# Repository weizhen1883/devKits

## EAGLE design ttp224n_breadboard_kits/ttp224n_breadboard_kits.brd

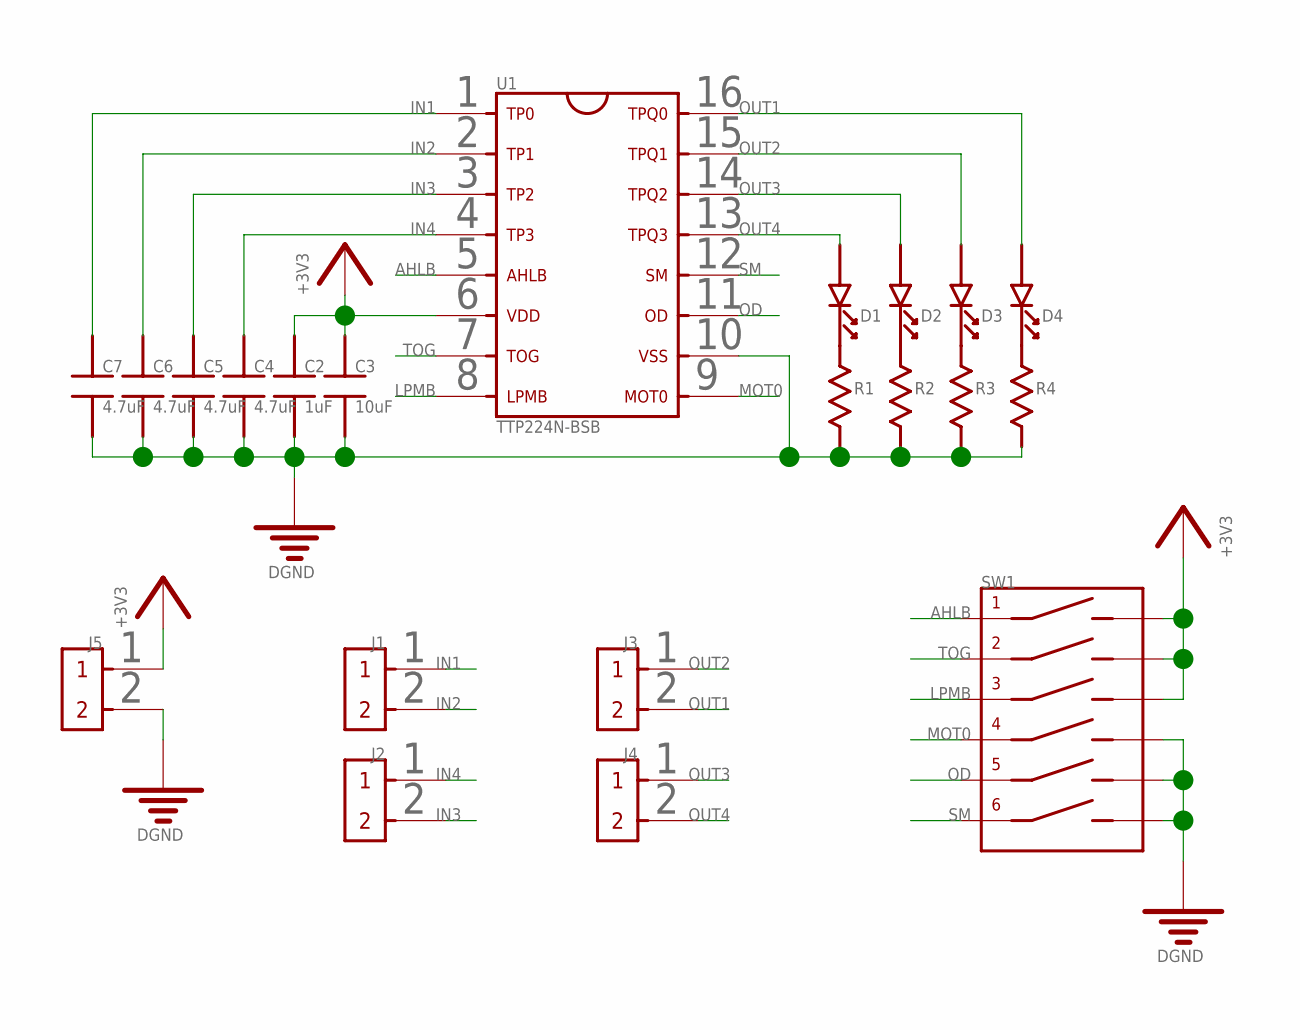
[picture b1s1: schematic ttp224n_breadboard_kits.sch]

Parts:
C2: 1uF; 0805
C3: 10uF; 0805
C4, C5, C6, C7: 4.7uF; 0805
D1, D2, D3, D4: LED-0805; 0805DIODE
J1, J2, J3, J4, J5: 2PIN_HEADER_PITCH2.54MM_TH
R1, R2, R3, R4: RESISTOR_0805; 0805
SW1: DIP_SWITCH_6PIN-219-6MST; DIP_SW_219-6MST
U1: TTP224N-BSB; SSOP-16

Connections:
+3V3: C2.1, C3.1, J5.1, SW1.2 (1.1), SW1.4 (2.1), SW1.6 (3.1), U1.6
AHLB: SW1.1 (1.0), U1.5
DGND: C2.2, C3.2, C4.2, C5.2, C6.2, C7.2, J5.2, R1.2, R2.2, R3.2, R4.2, SW1.8 (4.1), SW1.10 (5.1), SW1.12 (6.1), U1.10
IN1: C7.1, J1.1, U1.1
IN2: C6.1, J1.2, U1.2
IN3: C5.1, J2.2, U1.3
IN4: C4.1, J2.1, U1.4
LPMB: SW1.5 (3.0), U1.8
MOT0: SW1.7 (4.0), U1.9
unnamed: D1.1 (K), R1.1
unnamed: D2.1 (K), R2.1
unnamed: D3.1 (K), R3.1
unnamed: D4.1 (K), R4.1
OD: SW1.9 (5.0), U1.11
OUT1: D4.2 (A), J3.2, U1.16
OUT2: D3.2 (A), J3.1, U1.15
OUT3: D2.2 (A), J4.1, U1.14
OUT4: D1.2 (A), J4.2, U1.13
SM: SW1.11 (6.0), U1.12
TOG: SW1.3 (2.0), U1.7

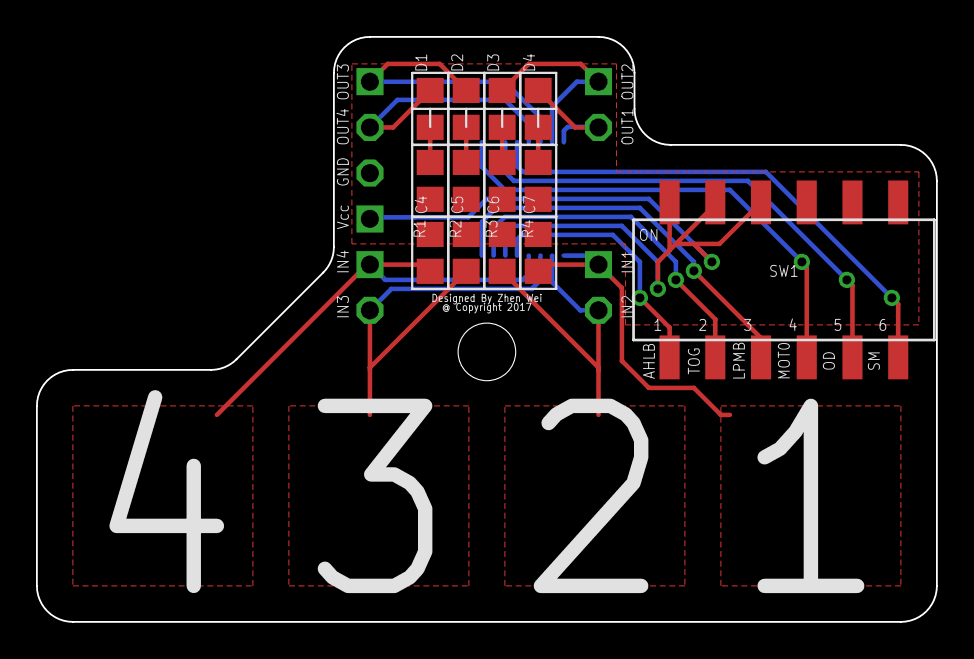
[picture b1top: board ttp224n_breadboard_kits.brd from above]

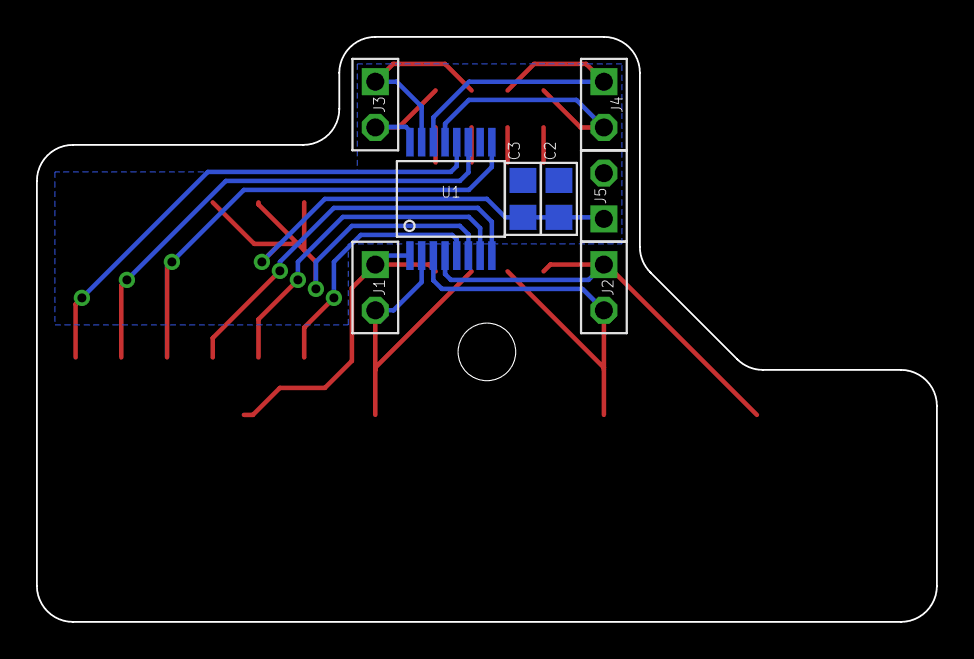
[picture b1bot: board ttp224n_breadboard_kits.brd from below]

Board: 2 copper layers, 50.0 x 32.5 mm, 21 parts (8 on the bottom side), 20 nets.

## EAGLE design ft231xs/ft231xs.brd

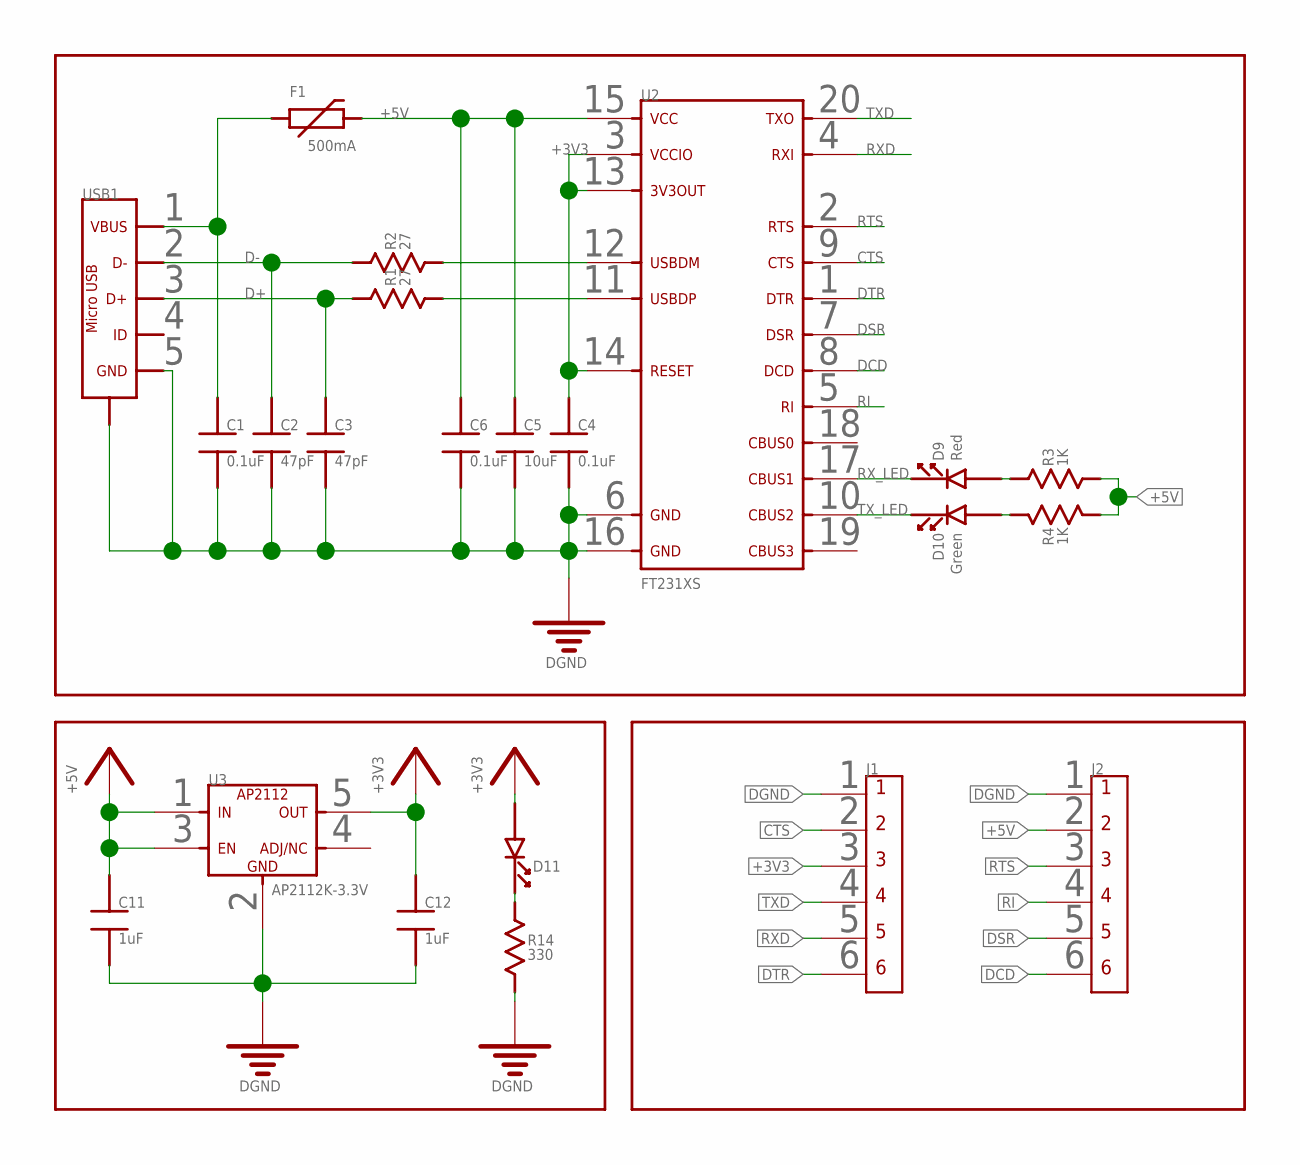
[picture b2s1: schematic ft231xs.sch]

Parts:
C1, C4, C6: 0.1uF; 0805
C2, C3: 47pF; 0805
C5: 10uF; 0805
C11, C12: 1uF; 0805
D9: Red; 0805DIODE
D10: Green; 0805DIODE
D11: LED-0805; 0805DIODE
F1: 500mA; 0805
J1, J2: 6PIN_HEADER_PITCH2.54MM_TH
R1, R2: 27; 0805
R3, R4: 1K; 0805
R14: 330; 0805
U2: FT231XS_SSOP20; SSOP-20
U3: AP2112K-3.3V; SOT-23-5
USB1: USB-2.0-MICRO_SMD_SMD; MICRO-USB-B-SMD-SMD

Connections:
+3V3: C4.1, C12.1, D11.2 (A), J1.3, U2.3, U2.13, U2.14, U3.5
+5V: C5.1, C6.1, C11.1, F1.2, J2.2, R3.2, R4.2, U2.15, U3.1, U3.3
CTS: J1.2, U2.9
D+: C3.1, R1.1, USB1.3 (D+)
D-: C2.1, R2.1, USB1.2 (D-)
DCD: J2.6, U2.8
DGND: C1.2, C2.2, C3.2, C4.2, C5.2, C6.2, C11.2, C12.2, J1.1, J2.1, R14.2, U2.6, U2.16, U3.2, USB1.5 (GND), USB1.M1 (SHIELD), USB1.M2 (SHIELD), USB1.M3 (SHIELD), USB1.M4 (SHIELD), USB1.S1 (SHIELD), USB1.S2 (SHIELD)
DSR: J2.5, U2.7
DTR: J1.6, U2.1
unnamed: R2.2, U2.12
unnamed: R1.2, U2.11
unnamed: D9.2 (A), R3.1
unnamed: D10.2 (A), R4.1
unnamed: D11.1 (K), R14.1
RI: J2.4, U2.5
RTS: J2.3, U2.2
RXD: J1.5, U2.4
RX_LED: D9.1 (K), U2.17
TXD: J1.4, U2.20
TX_LED: D10.1 (K), U2.10
VBUS: C1.1, F1.1, USB1.1 (VBUS)

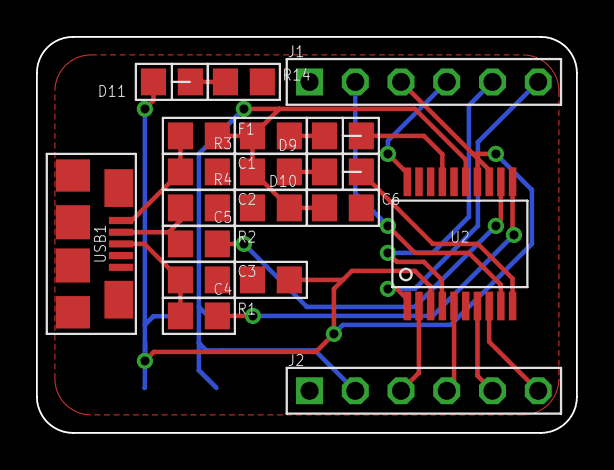
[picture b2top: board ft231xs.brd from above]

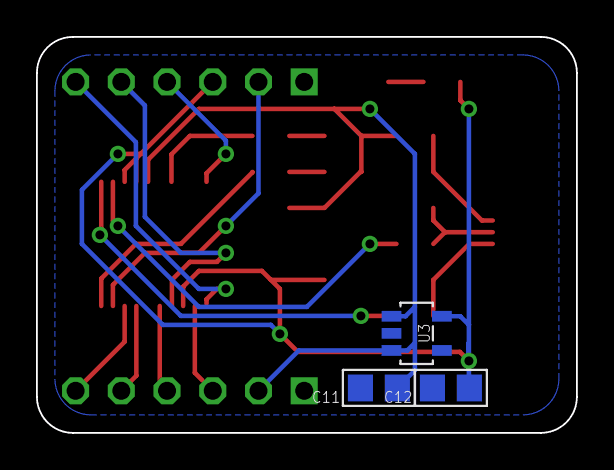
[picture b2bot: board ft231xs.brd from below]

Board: 2 copper layers, 30.0 x 22.0 mm, 22 parts (3 on the bottom side), 21 nets.

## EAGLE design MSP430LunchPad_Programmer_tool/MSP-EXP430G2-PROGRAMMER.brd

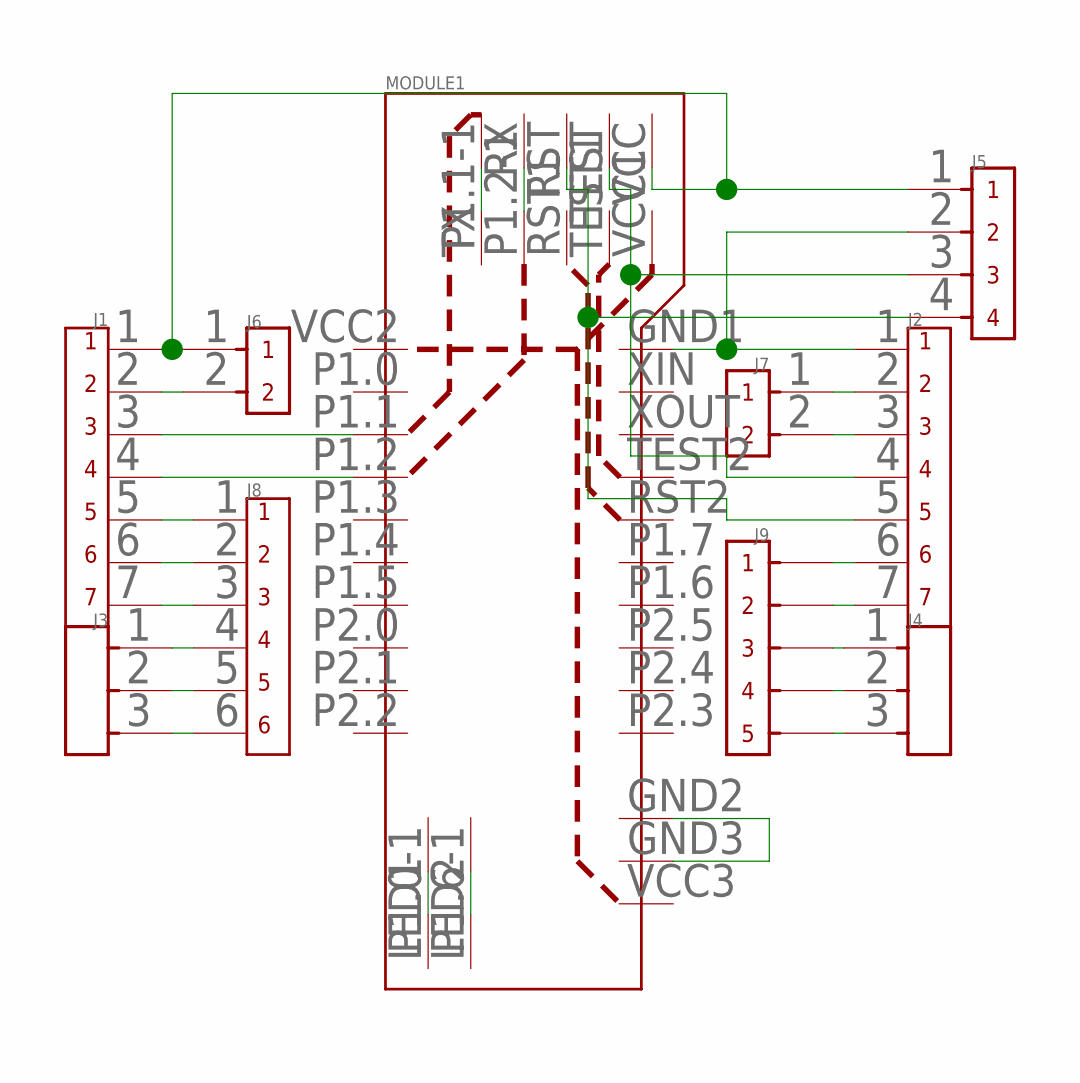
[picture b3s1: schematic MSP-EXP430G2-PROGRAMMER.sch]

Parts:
J1, J2: 7PIN_HEADER_PITCH2.54MM_TH
J3, J4: 3PIN_HEADER_PITCH2.54MM_TH
J5: 4PIN_HEADER_PITCH2.54MM_TH
J6, J7: 2PIN_HEADER_PITCH2.54MM_TH
J8: 6PIN_HEADER_PITCH2.54MM_TH
J9: 5PIN_HEADER_PITCH2.54MM_TH
MODULE1: MSP-EXP430G2-SHELL

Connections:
DGND: J2.1, J5.2, MODULE1.GND1, MODULE1.GND2, MODULE1.GND3
unnamed: J1.3, MODULE1.P1.1
unnamed: J1.4, MODULE1.P1.2
unnamed: MODULE1.P1.1-1, MODULE1.TX
unnamed: MODULE1.P1.2-1, MODULE1.RX
unnamed: J1.2, J6.2
unnamed: J1.5, J8.1
unnamed: J1.6, J8.2
unnamed: J1.7, J8.3
unnamed: J3.1, J8.4
unnamed: J3.2, J8.5
unnamed: J3.3, J8.6
unnamed: J2.2, J7.1
unnamed: J2.3, J7.2
unnamed: J2.6, J9.1
unnamed: J2.7, J9.2
unnamed: J4.1, J9.3
unnamed: J4.2, J9.4
unnamed: J4.3, J9.5
unnamed: MODULE1.LED1 (LED0), MODULE1.P1.0-1
unnamed: MODULE1.LED2 (LED1), MODULE1.P1.6-1
RESET: J2.5, J5.4, MODULE1.RST
TEST: J2.4, J5.3, MODULE1.TEST
VCC: J1.1, J5.1, J6.1, MODULE1.VCC

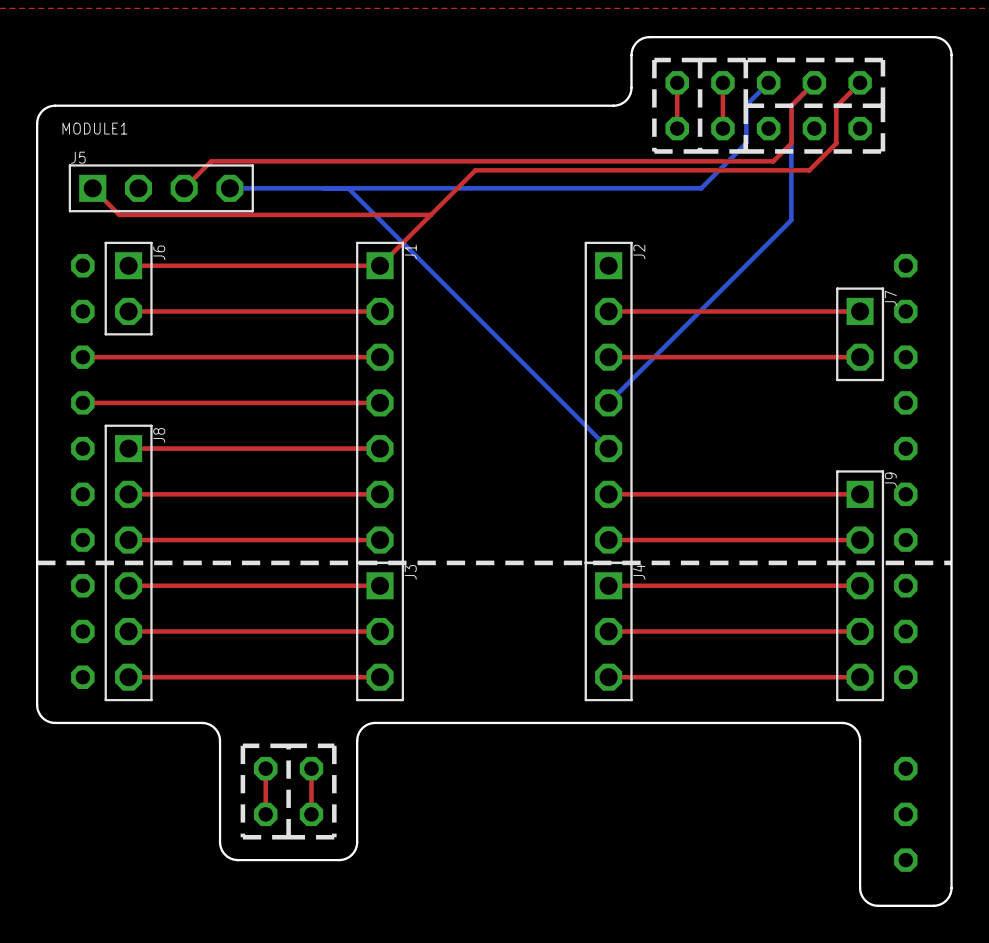
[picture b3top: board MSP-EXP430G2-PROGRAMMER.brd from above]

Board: 2 copper layers, 50.8 x 48.3 mm, 10 parts (0 on the bottom side), 24 nets.

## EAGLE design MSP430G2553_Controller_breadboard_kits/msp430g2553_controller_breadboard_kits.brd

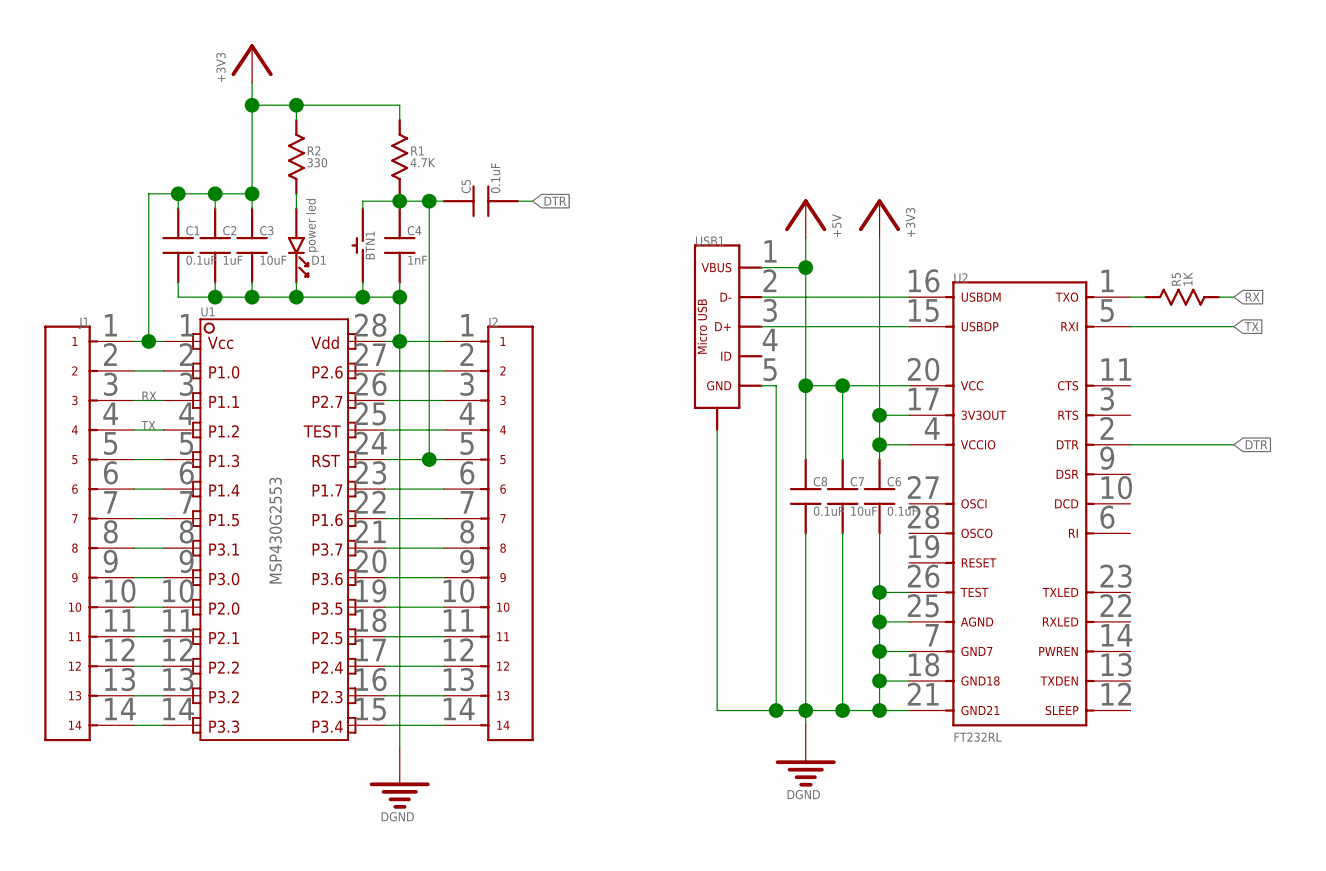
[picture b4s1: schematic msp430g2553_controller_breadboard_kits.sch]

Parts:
BTN1: BTN_NORMAL_OFF_6_3.5_SMD; BTN_6_3.5_SMD
C1, C5, C6, C8: 0.1uF; 0805
C2: 1uF; 0805
C3, C7: 10uF; 0805
C4: 1nF; 0805
D1: power led; 0805DIODE
J1, J2: 14PIN_HEADER_PITCH2.54MM_TH
R1: 4.7K; 0805
R2: 330; 0805
R5: 1K; 0805
U1: MSP430G2553_24IO_28PIN_TSSOP; TSSOP-28
U2: FT232RL_SSOP28; SSOP-28
USB1: USB-2.0-MICRO_SMD_SMD; MICRO-USB-B-SMD-SMD

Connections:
+3V3: C1.1, C2.1, C3.1, C6.1, J1.1, R1.1, R2.1, U1.1, U2.4, U2.17
+5V: C7.1, C8.1, U2.20, USB1.1 (VBUS)
DGND: BTN1.1, C1.2, C2.2, C3.2, C4.2, C6.2, C7.2, C8.2, D1.1 (K), J2.1, U1.28, U2.7, U2.18, U2.21, U2.25, U2.26, USB1.5 (GND), USB1.S1 (SHIELD), USB1.S2 (SHIELD)
DTR: C5.2, U2.2
unnamed: D1.2 (A), R2.2
P1.0: J1.2, U1.2
P1.3: J1.5, U1.5
P1.4: J1.6, U1.6
P1.5: J1.7, U1.7
P1.7: J2.6, U1.23
P2.0: J1.10, U1.10
P2.1: J1.11, U1.11
P2.2: J1.12, U1.12
P2.3: J2.13, U1.16
P2.4: J2.12, U1.17
P2.5: J2.11, U1.18
P2.6: J2.2, U1.27
P2.7: J2.3, U1.26
P3.0: J1.9, U1.9
P3.1: J1.8, U1.8
P3.2: J1.13, U1.13
P3.3: J1.14, U1.14
P3.4: J2.14, U1.15
P3.5: J2.10, U1.19
P3.6: J2.9, U1.20
P3.7: J2.8, U1.21
P`.6: J2.7, U1.22
RST: BTN1.2, C4.1, C5.1, J2.5, R1.2, U1.24
RX: J1.3, R5.2, U1.3
TEST: J2.4, U1.25
TX: J1.4, U1.4, U2.5
TXO: R5.1, U2.1
USBDM: U2.16, USB1.2 (D-)
USBDP: U2.15, USB1.3 (D+)

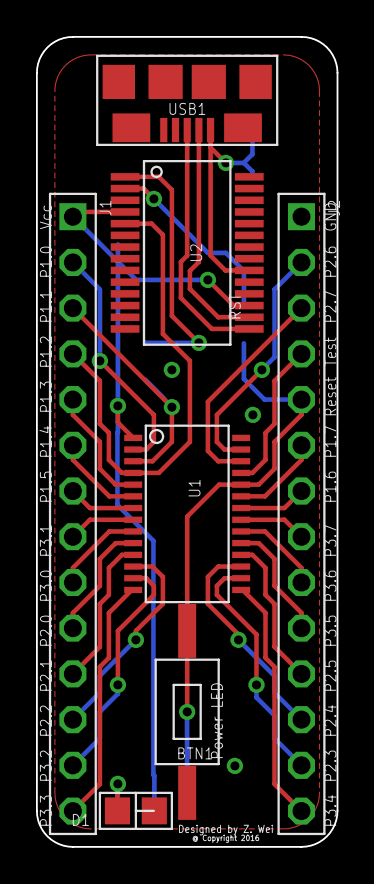
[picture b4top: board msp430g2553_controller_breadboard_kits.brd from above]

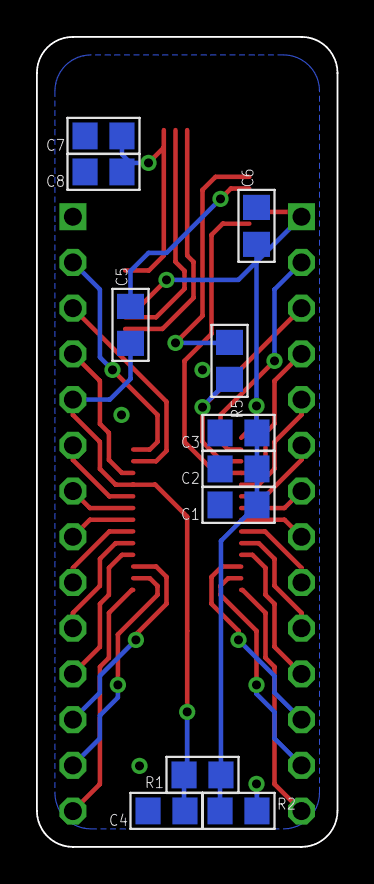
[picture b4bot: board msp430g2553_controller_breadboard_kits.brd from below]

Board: 2 copper layers, 16.7 x 45.0 mm, 18 parts (11 on the bottom side), 34 nets.

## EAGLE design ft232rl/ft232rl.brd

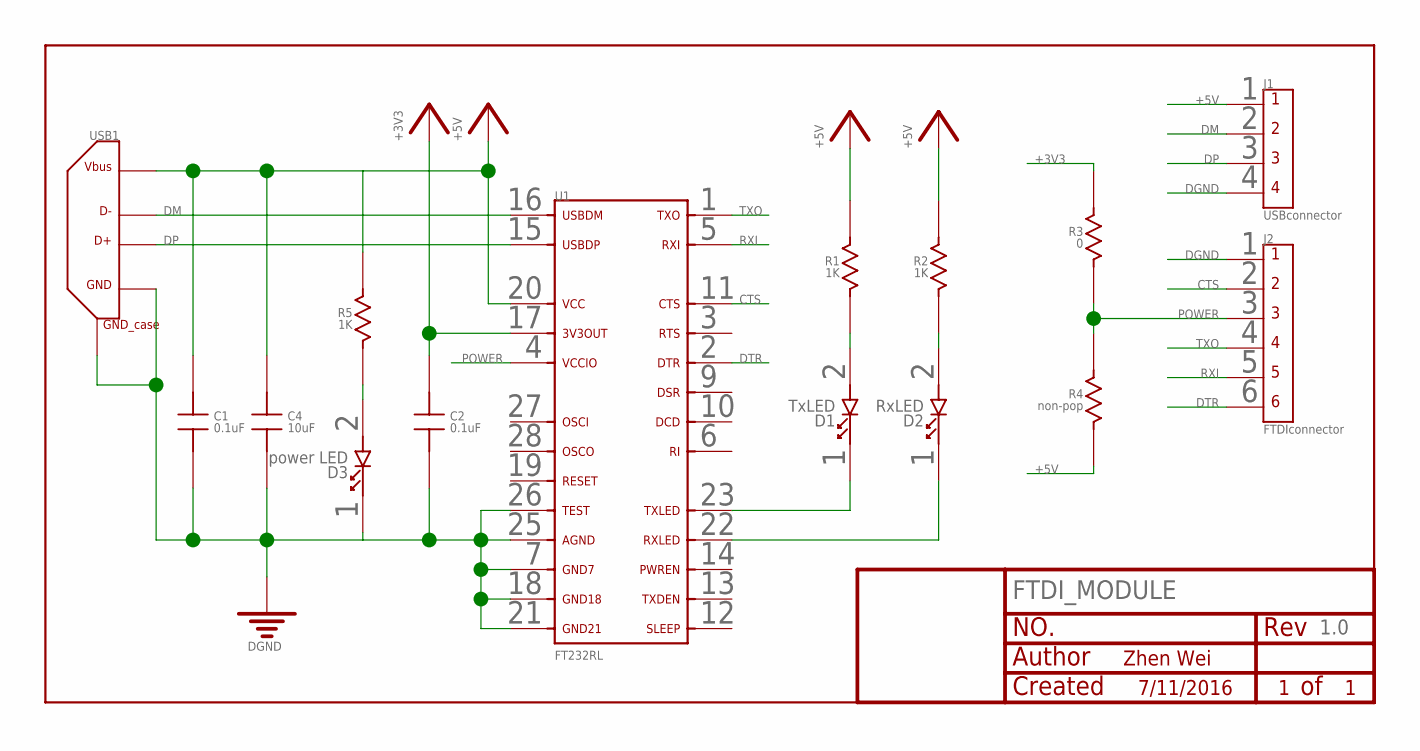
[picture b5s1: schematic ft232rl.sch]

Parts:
C1, C2: 0.1uF; 0805
C4: 10uF; 0805
D1: TxLED; 0805DIODE
D2: RxLED; 0805DIODE
D3: power LED; 0805DIODE
FTDI_MODULE: 1.0; IVANI-LABEL
J1: USBconnector; 4PIN_HEADER_PITCH2.54MM_TH
J2: FTDIconnector; 6PIN_HEADER_PITCH2.54MM_TH
R1, R2, R5: 1K; 0805
R3: 0; 0805
R4: non-pop; 0805
U1: FT232RL; SSOP-28
USB1: USB-1.X/2.0-STANDARDTYPEA-TH; USB-A-TH

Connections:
+3V3: C2.1, R3.1, U1.17
+5V: C1.1, C4.1, J1.1, R1.1, R2.1, R4.2, R5.1, U1.20, USB1.1 (VBUS)
CTS: J2.2, U1.11
DGND: C1.2, C2.2, C4.2, D3.1, J1.4, J2.1, U1.7, U1.18, U1.21, U1.25, U1.26, USB1.4 (GND), USB1.CASE1 (GND_CASE), USB1.CASE2 (GND_CASE)
DM: J1.2, U1.16, USB1.2 (D-)
DP: J1.3, U1.15, USB1.3 (D+)
DTR: J2.6, U1.2
unnamed: D1.2, R1.2
unnamed: D2.2, R2.2
unnamed: D3.2, R5.2
POWER: J2.3, R3.2, R4.1, U1.4
RXI: J2.5, U1.5
RXLED: D2.1, U1.22
TXLED: D1.1, U1.23
TXO: J2.4, U1.1

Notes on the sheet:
Zhen Wei
7/11/2016

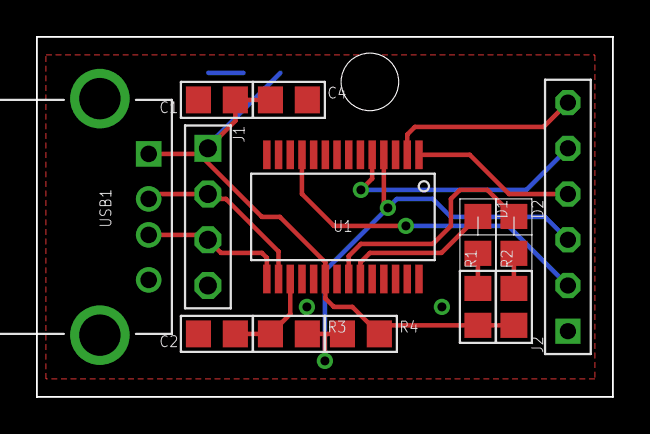
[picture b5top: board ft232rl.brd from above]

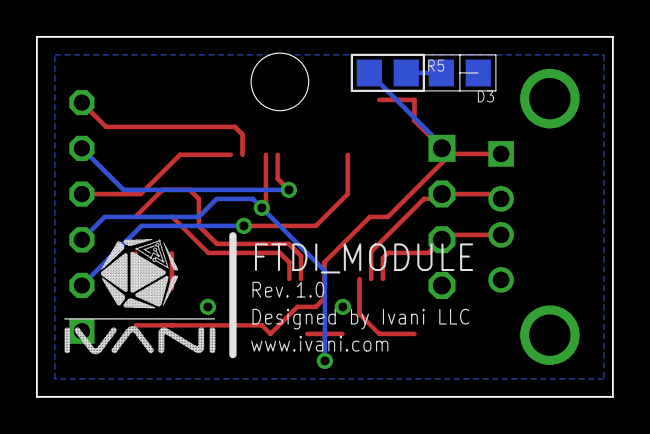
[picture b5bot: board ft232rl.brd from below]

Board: 2 copper layers, 32.0 x 20.0 mm, 16 parts (3 on the bottom side), 15 nets.

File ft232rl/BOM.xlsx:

Parts | Value | Footprint | Parts Number | Price | Quantity | Total
C1,C2 | 0.1uF | 0805 | CL21F104ZBCNNNC | 0.1 | 2 | 0.2
C4 | 10uF | 0805 | CL21F106ZQFNNNE | 0.14000000000000001 | 1 | 0.14000000000000001
R1,R2,R5 | 1KΩ | 0805 | RC0805FR-071KL | 0.1 | 3 | 0.30000000000000004
R3 | 0Ω | 0805 | RC0805JR-070RL | 0.1 | 1 | 0.1
R4 | non-pop | 0805 |  | 0 | 1 | 0
D1,D3 | Green LEDs | 0805 | LG R971-KN-1 | 0.26 | 2 | 0.52
D2 | Red LEDs | 0805 | LH R974-LP-1 | 0.26 | 1 | 0.26
U1 | FT232RL | SSOP28 | FT232RL-REEL | 4.5 | 1 | 4.5
J1 | 4pin 0.100" header | CON-HEADER-100 |  |  | 1 | 0
J2 | 6pin 0.100" header | CON-HEADER-101 |  |  | 1 | 0
USB1 | USB-2.0-typeA-female |  |  |  | 1 | 0
 |  |  |  |  | Total: | 5.82

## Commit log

2016-10-31 done the msp430g2553 breadboard kits
2016-10-31 the ft231xs module is keeping going
2016-10-31 start working
2016-10-31 start working on ttp224n devkits
2016-10-31 create the msp430g2553 dev branch
2016-10-31 the ttp224n breadboard kits is done
2017-02-02 add 232 module and finish the ft231
2017-03-11 done the design
2017-03-12 make the cam work for pc
2017-03-29 update values
2017-05-06 backup for system change
2017-05-08 launchpad programmer done
2017-05-08 the ft231xs is ready
2019-05-10 update the ttp224 touchpad module
2019-05-10 add gitignore
2019-05-10 make the change and ttp224n_breadboard_kits is ready to go

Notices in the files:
MSP430G2553_Controller_breadboard_kits/msp430g2553_controller_breadboard_kits.brd:
@ Copyright 2016
ttp224n_breadboard_kits/ttp224n_breadboard_kits.brd:
@ Copyright 2017
